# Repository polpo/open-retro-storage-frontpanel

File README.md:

# Open Retro Storage Front Panel

A physical control and web interface for retro storage emulator projects including [PicoIDE](https://github.com/polpo/picoide) and [BlueSCSI](https://github.com/BlueSCSI/BlueSCSI-v2), based on the ESP32-C3 microcontroller.

## Overview

The Open Retro Storage Front Panel provides a user-friendly interface for browsing, selecting, and managing drive images for storage emulators live on the device. It features:

- **SPI or I2C (Qwiic) connection to main board**
- **SPI OLED Display**: 128x64 1.3" screen for menu navigation and status display
- **4-Way Navigation**: Physical buttons for browsing drive images and settings
- **WiFi Interface**: Web-based control for changing drive images, adjusting settings, uploading new images, and firmware updates
- **3.5" Drive Bay Enclosure**: Designed for internal or external-facing mounting in standard drive bays

## Project Structure

```
open-retro-storage-frontpanel/
├── sw-frontpanel/       # Firmware source code
├── hw-frontpanel-3.5/   # PCB hardware design
└── enclosure/           # 3D printable enclosure design
```

### sw-frontpanel

ESP32-C3 firmware built with the ESP-IDF SDK (v5.5.1+).

**Features:**
- SPI or I2C (Qwiic) communication with host storage emulator
- Menu system for drive image browsing and selection
- WiFi client and access point modes with mDNS
- Embedded web server with REST API
- OTA firmware updates with SHA256 verification
- WS2812B addressable LED support
- Screen saver, auto-dim, or auto-off to preserve OLED display life

### hw-frontpanel-3.5

KiCad design files for the front panel PCB.

**Main components:**
- ESP32-C3-MINI-1 module
- SH1107 1.3" OLED display (SPI interface)
- SK6812MINI-E (WS2812 compatible) addressable RGB LED
- Navigation buttons (either 1-piece silicone rubber dome or plastic button caps w/ individual domes)
- JST-SH connectors for QWIIC/I2C communication with host, external activity LED input, and development debugging, 0.5mm FFC connector for SPI communication with host, and Tag-Connect footprint for initial programming in production

Connector pinouts:

SPI (0.5mm FFC, 12 pin):

| Pin | Function |
|-----|----------|
| 1   | Activity LED in |
| 2   | GND |
| 3   | SPI CS |
| 4   | GND |
| 5   | SPI CLK |
| 6   | GND |
| 7   | SPI RX (MISO) |
| 8   | GND |
| 9   | SPI TX (MOSI) |
| 10  | GND |
| 11  | +3.3V |
| 12  | +3.3V |

I2C/Qwiic (JST-SH, 4 pin):

| Pin | Function |
|-----|----------|
| 1   | GND|
| 2   | +3.3V |
| 3   | SDA |
| 4   | SCL |

ACT (JST-SH, 2 pin):

| Pin | Function |
|-----|----------|
| 1   | Activity LED in |
| 2   | GND |

Production files for JLCPCB assembly are included in `jlcpcb/production_files/`.

### enclosure

FreeCAD design for a 3.5" drive bay enclosure with STEP and STL exports for 3D printing.

**Included parts:**
- Main enclosure body
- Button caps
- Light pipe for activity/status LED
- Silicone button option

## Web Interface

The front panel hosts a web interface accessible at `http://picoide.local` (or via IP address) providing:

- Current drive image status
- Directory browsing
- File upload/download
- Config .ini file editing
- Image selection/ejection
- Firmware status and updates

## Licensing

| Component | License |
|-----------|---------|
| sw-frontpanel | [GPL-2.0-only](sw-frontpanel/LICENSE) |
| hw-frontpanel-3.5 | [CERN-OHL-S-2.0](hw-frontpanel-3.5/LICENSE) |
| enclosure | [CERN-OHL-S-2.0](enclosure/LICENSE) |

## Credits

- Firmware by Ian Scott in collaboration with Eric Helgeson.
- Board design by Ian Scott with input from Jason Merrill.
- Enclosure by Jason Merrill.

## Open source components

- [ESP-IDF](https://github.com/espressif/esp-idf) development framework for ESP32
- [u8g2](https://github.com/olikraus/u8g2) graphics library for OLED
- [u8g2-hal-esp-idf](https://github.com/mkfrey/u8g2-hal-esp-idf) u8g2 HAL layer for ESP-IDF

## Contributing

Contributions are welcome! Please ensure any firmware contributions maintain GPL v2 compatibility and hardware contributions are compatible with CERN-OHL-S v2.

## Building the firmware

Make sure you check out this repository with submodules. If it's already checked out, `git submodule update --init` will fetch them. See [sw-frontpanel/BUILD.md](sw-frontpanel/BUILD.md) for detailed instructions including configuration of target type (PicoIDE/BlueSCSI, SPI/I2C).

## Programming the firmware

For normal firmware upgrades, the front panel can be upgraded via the web interface. But if you're building from scratch or need to recover a bricked unit, you'll need to program the ESP32-C3 by UART bootloader.

There are two footprints on the board that can be used to program it: J4 (prog) and J6 (dbg). J4 is a [Tag-Connect](https://www.tag-connect.com/) footprint, using the [TC2030-IDC-NL](https://www.tag-connect.com/product/tc2030-idc-nl) connector. The pinout matches the 6-pin connector on the [Espressif ESP-PROG 2](https://docs.espressif.com/projects/esp-dev-kits/en/latest/other/esp-prog-2/user_guide.html) programmer:

| Pin | Function |
|-----|----------|
| 1   | EN (RTS) |
| 2   | +3.3V |
| 3   | TX |
| 4   | GND |
| 5   | RX |
| 6   | IO0 (DTR) |

J6 is a JST SH 5-pin connector with the following pinout (pins numbered ascending left to right):

| Pin | Function |
|-----|----------|
| 1   | GND |
| 2   | RX |
| 3   | TX |
| 4   | EN (RTS) |
| 5   | IO0 (DTR) |

Note that J6 does not carry +3.3V so you'll have to provide it on the SPI or I2C (QWIIC) connector.

Note that the TX signal is shared with the LED input, so if it is driven via the SPI connector programming will not be possible.

Use `esptool` or `esp.py program` to program the firmware after it has been built.

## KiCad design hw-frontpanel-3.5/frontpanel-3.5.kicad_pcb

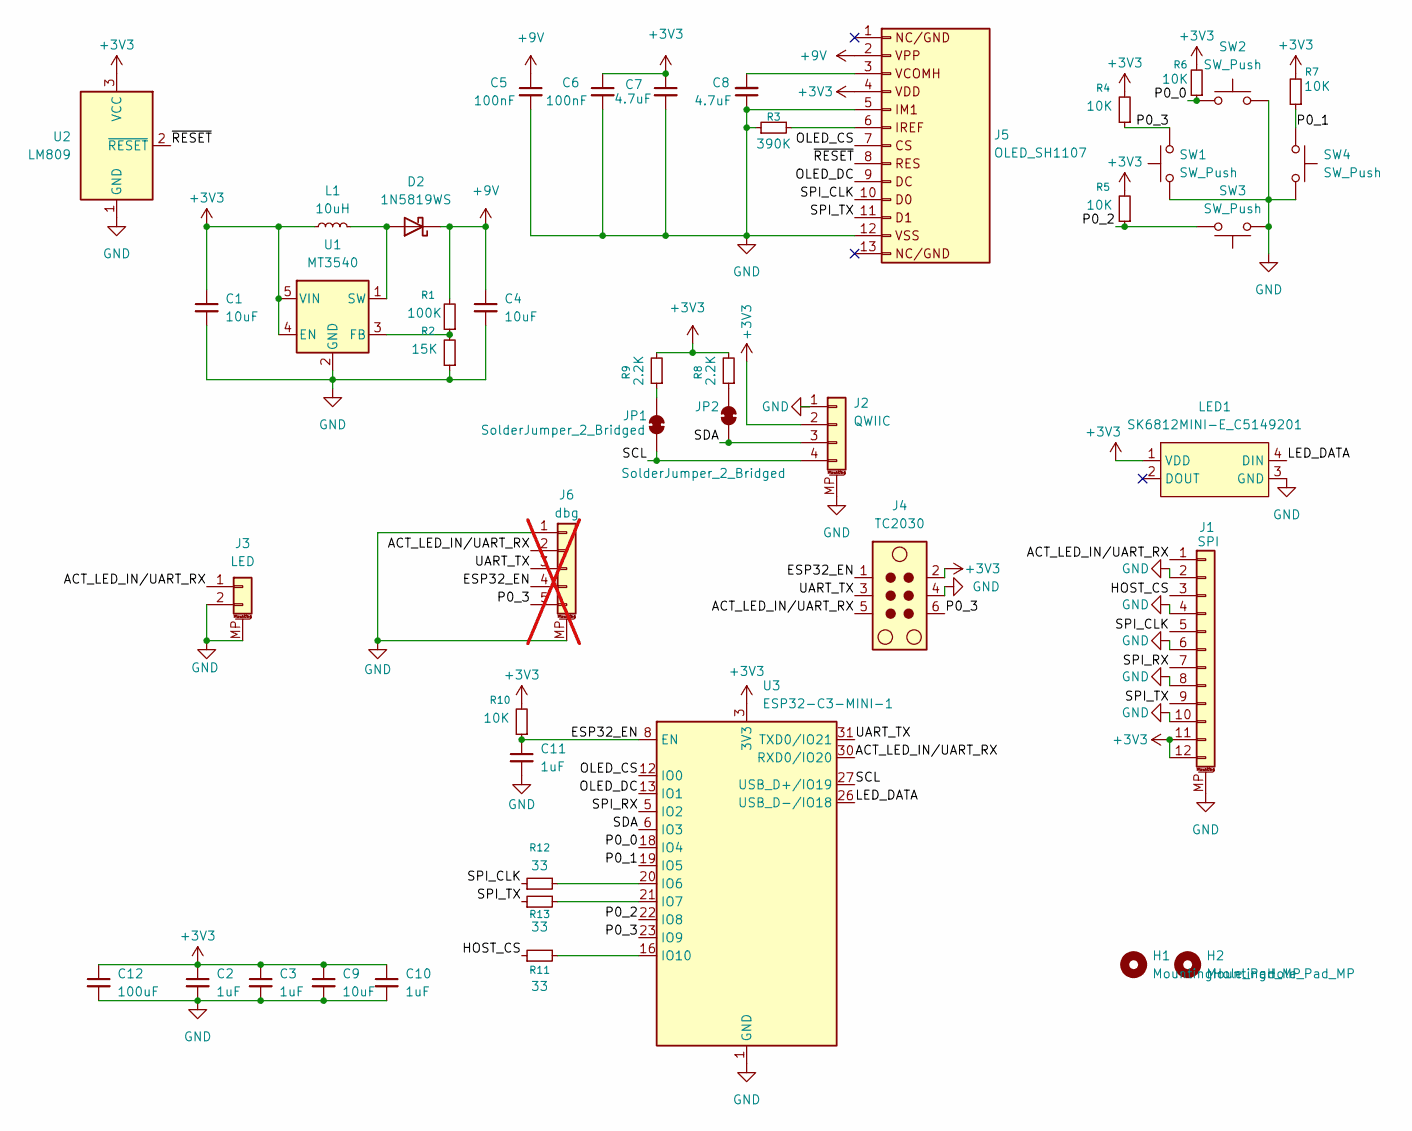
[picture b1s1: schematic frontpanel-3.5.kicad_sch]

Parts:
C1, C4: 10uF; C_0603_1608Metric; LCSC C96446
C2, C3, C10, C11: 1uF; C_0402_1005Metric; LCSC C15849
C5, C6: 100nF; C_0402_1005Metric; LCSC C14663
C7, C8: 4.7uF; C_0603_1608Metric; LCSC C19666
C9: 10uF; C_0603_1608Metric
C12: 100uF; C_1206_3216Metric; LCSC C96123
D2: 1N5819WS; D_SOD-323; LCSC C191023
H1, H2: MountingHole_Pad_MP; MountingHole_2.2mm_M2
J1: SPI; FPC-SMD_12P-L11.5-W2.0-P0.50; LCSC C2874482
J2: QWIIC; JST_SH_BM04B-SRSS-TB_1x04-1MP_P1.00mm_Vertical; LCSC C23390346
J3: LED; JST_SH_BM02B-SRSS-TB_1x02-1MP_P1.00mm_Vertical; LCSC C22438427
J4: TC2030; Tag-Connect_TC2030-IDC-NL_2x03_P1.27mm_Vertical
J5: OLED_SH1107; OLED-SMD_N130-6428TSWOG01-H13
J6: dbg; JST_SH_BM05B-SRSS-TB_1x05-1MP_P1.00mm_Vertical; LCSC C22438427; not fitted
JP1, JP2: SolderJumper_2_Bridged; SolderJumper-2_P1.3mm_Bridged_RoundedPad1.0x1.5mm
L1: 10uH; L_0805_2012Metric; LCSC C1046
LED1: SK6812MINI-E_C5149201; LED-SMD_L3.2-W2.8-LS5.9_SK6812MINI-E; LCSC Part C5149201
R1: 100K; R_0402_1005Metric; LCSC C25803
R2: 15K; R_0402_1005Metric; LCSC C22809
R3: 390K; R_0402_1005Metric; LCSC C23150
R4, R5, R6, R7, R10: 10K; R_0402_1005Metric; LCSC C25804
R8, R9: 2.2K; R_0402_1005Metric; LCSC C4190
R11, R12, R13: 33; R_0402_1005Metric
SW1, SW2, SW3, SW4: SW_Push; button-contact-round-5mm
U1: MT3540; SOT-23-5; LCSC C181744
U2: LM809; SOT-23; LCSC C5379074
U3: ESP32-C3-MINI-1; ESP32-C6-MINI-1; LCSC C2838502

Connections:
+3V3: C1.1, C2.1, C3.1, C6.1, C7.1, C9.1, C10.1, C12.1, J1.11, J1.12, J2.2, J4.2, J5.4, L1.1, LED1.1 (VDD), R4.2, R5.2, R6.2, R7.2, R8.2, R9.2, R10.2, U1.4 (EN), U1.5 (VIN), U2.3 (VCC), U3.3 (3V3)
+9V: C4.1, C5.1, D2.1 (K), J5.2, R1.2
/ACT_LED_IN/UART_RX: J1.1, J3.1, J4.5, J6.2, U3.30 (RXD0/IO20)
/ESP32_EN: C11.1, J4.1, J6.4, R10.1, U3.8 (EN)
/HOST_CS: J1.3, R11.1
/LED_DATA: LED1.4 (DIN), U3.26 (USB_D-/IO18)
/OLED_CS: J5.7, U3.12 (IO0)
/OLED_DC: J5.9, U3.13 (IO1)
/P0_0: R6.1, SW2.1, U3.18 (IO4)
/P0_1: R7.1, SW4.1, U3.19 (IO5)
/P0_2: R5.1, SW3.2, U3.22 (IO8)
/P0_3: J4.6, J6.5, R4.1, SW1.2, U3.23 (IO9)
/SCL: J2.4, JP1.1 (A), U3.27 (USB_D+/IO19)
/SDA: J2.3, JP2.1 (A), U3.6 (IO3)
/SPI_CLK: J1.5, J5.10, R12.1
/SPI_RX: J1.7, U3.5 (IO2)
/SPI_TX: J1.9, J5.11, R13.1
/UART_TX: J4.3, J6.3, U3.31 (TXD0/IO21)
/~RESET: J5.8, U2.2 (~RESET)
GND: C1.2, C2.2, C3.2, C4.2, C5.2, C6.2, C7.2, C8.1, C9.2, C10.2, C11.2, C12.2, J1.2, J1.4, J1.6, J1.8, J1.10, J1.MP (MountPin), J2.1, J2.MP (MountPin), J3.2, J3.MP (MountPin), J4.4, J5.5, J5.12, J6.1, J6.MP (MountPin), LED1.3 (GND), R2.1, R3.1, SW1.1, SW2.2, SW3.1, SW4.2, U1.2 (GND), U2.1 (GND), U3.1 (GND), U3.2 (GND), U3.11 (GND), U3.14 (GND), U3.36 (GND), U3.37 (GND), U3.38 (GND), U3.39 (GND), U3.40 (GND), U3.41 (GND), U3.42 (GND), U3.43 (GND), U3.44 (GND), U3.45 (GND), U3.46 (GND), U3.47 (GND), U3.48 (GND), U3.49 (GND), U3.50 (GND), U3.51 (GND), U3.52 (GND), U3.53 (GND)
unnamed: D2.2 (A), L1.2, U1.1 (SW)
unnamed: C8.2, J5.3
unnamed: J5.6, R3.2
unnamed: JP1.2 (B), R9.1
unnamed: JP2.2 (B), R8.1
unnamed: R1.1, R2.2, U1.3 (FB)
unnamed: R12.2, U3.20 (IO6)
unnamed: R13.2, U3.21 (IO7)
unnamed: R11.2, U3.16 (IO10)

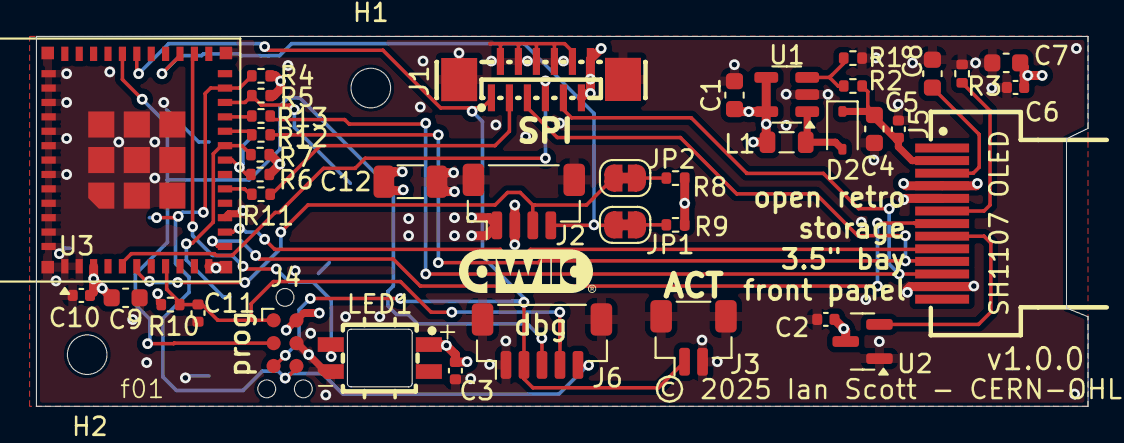
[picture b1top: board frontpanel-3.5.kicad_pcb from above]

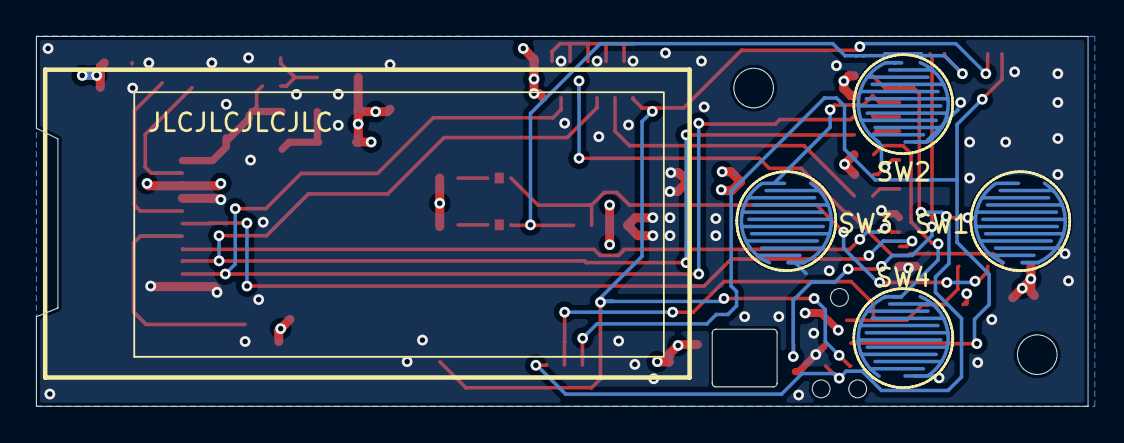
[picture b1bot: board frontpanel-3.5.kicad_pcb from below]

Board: 4 copper layers, 58.4 x 20.5 mm, 45 parts (4 on the bottom side), 29 nets.

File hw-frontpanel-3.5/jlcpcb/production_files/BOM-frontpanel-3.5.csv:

Comment,Designator,Footprint,LCSC,Quantity
100K,R1,R_0402_1005Metric,C25741,1
100nF,"C5,C6",C_0402_1005Metric,C307331,2
100uF,C12,C_1206_3216Metric,C96123,1
10K,"R10,R4,R5,R6,R7",R_0402_1005Metric,C25744,5
10uF,"C1,C4,C9",C_0603_1608Metric,C96446,3
10uH,L1,L_0805_2012Metric,C1046,1
15K,R2,R_0402_1005Metric,C25756,1
1N5819WS,D2,D_SOD-323,C191023,1
1uF,"C10,C11,C2,C3",C_0402_1005Metric,C52923,4
2.2K,"R8,R9",R_0402_1005Metric,C25879,2
33,"R11,R12,R13",R_0402_1005Metric,C25105,3
390K,R3,R_0402_1005Metric,C25782,1
4.7uF,"C7,C8",C_0603_1608Metric,C19666,2
ESP32-C3-MINI-1,U3,ESP32-C6-MINI-1,C2838502,1
LED,J3,JST_SH_BM02B-SRSS-TB_1x02-1MP_P1.00mm_Vertical,C7433438,1
LM809,U2,SOT-23,C5379074,1
MT3540,U1,SOT-23-5,C181744,1
QWIIC,J2,JST_SH_BM04B-SRSS-TB_1x04-1MP_P1.00mm_Vertical,C7433440,1
SK6812MINI-E_C5149201,LED1,LED-SMD_L3.2-W2.8-LS5.9_SK6812MINI-E,C5149201,1
SPI,J1,FPC-SMD_12P-L11.5-W2.0-P0.50,C11069,1

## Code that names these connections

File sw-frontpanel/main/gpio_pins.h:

// SPDX-License-Identifier: GPL-2.0-only
//
//  Copyright (C) 2025  Ian Scott
//
//  This program is free software; you can redistribute it and/or modify it
//  under the terms of the GNU General Public License (as published by the
//  Free Software Foundation) version 2, dated June 1991.
//
//  This program is distributed in the hope that it will be useful,
//  but WITHOUT ANY WARRANTY; without even the implied warranty of
//  MERCHANTABILITY or FITNESS FOR A PARTICULAR PURPOSE.  See the
//  GNU General Public License for more details.
//
//  You should have received a copy of the GNU General Public License along
//  with this program; if not, see <https://www.gnu.org/licenses/>.

#pragma once

#include "driver/gpio.h"
#include "sdkconfig.h"

#ifdef CONFIG_PANEL_BOARD_C3_SUPERMINI

// ESP32-C3 SuperMini (DIY, web UI only).
//
// That board brings out GPIO0-10, GPIO20 and GPIO21 and nothing else: GPIO18
// and GPIO19 are wired to its USB-C data lines, and GPIO11-17 are the module's
// SPI flash. Three of the remaining pins are spoken for by the board itself -
// GPIO8 drives the onboard blue LED, GPIO9 is the BOOT button, GPIO2 carries
// the strapping pull-up - and GPIO20/21 are the UART console. That leaves
// eight: GPIO0, 1, 3, 4, 5, 6, 7 and 10.
//
// Both host transports get their own pins, so one image runs on every main
// board. That spends all eight, which is why this board has no OLED
// (CONFIG_PANEL_NO_DISPLAY) and no navigation buttons
// (CONFIG_PANEL_NO_BUTTONS) - the web UI drives it instead.
//
// The SPI pins deliberately avoid the SPI2 IO_MUX set (MISO 2, CLK 6, MOSI 7,
// CS 10). IO_MUX would allow 80 MHz against the GPIO matrix's 40, and the host
// link runs at 10 - so there is nothing to win, and IO_MUX MISO would land on
// GPIO2, whose strapping level a host driving the line at reset could hold low.

// Host interface, I2C (BlueSCSI v2): GPIO3 -> host GPIO16,
// GPIO10 -> host GPIO17, plus 2.2k pull-ups to 3V3 on both.
#define PIN_SDA         GPIO_NUM_3
#define PIN_SCL         GPIO_NUM_10

// Host interface, SPI (BlueSCSI Ultra/Ultra Wide, PicoIDE).
//
// PicoIDE's 12-pin panel ribbon. RX and TX are named from the PicoIDE side,
// so they cross. A ground sits between every signal; tie them all on a long
// ribbon to keep the 10 MHz clock quiet.
//
//   1, 2            3V3       3V3 (the panel runs off this)
//   3, 5, 7, 9, 11  GND       GND
//   4               SPI_RX    GPIO7  (MOSI)
//   6               SPI_TX    GPIO5  (MISO)
//   8               SPI_CLK   GPIO6
//   10              SPI_CS    GPIO4
//   12              ACT_LED   GPIO0
#define PIN_SPI_CLK     GPIO_NUM_6
#define PIN_SPI_MOSI    GPIO_NUM_7
#define PIN_SPI_MISO    GPIO_NUM_5
#define PIN_HOST_CS     GPIO_NUM_4

// Activity indicator input (from main board). Unconnected on most DIY builds,
// so gpio_handler pulls it up - a floating pin would storm the edge ISR.
#define PIN_ACT_IN      GPIO_NUM_0

// LED output (WS2812B addressable LED strip), optional.
#define PIN_LED_OUT     GPIO_NUM_1

// UART interface (USB-C console)
#define PIN_UART_TX     GPIO_NUM_21

// No OLED on this board. These stay defined so the display paths still
// compile; CONFIG_PANEL_NO_DISPLAY means they are never driven.
#define PIN_OLED_CS     GPIO_NUM_NC
#define PIN_OLED_DC     GPIO_NUM_NC

#else

// OLED Display control pins (SPI mode)
#define PIN_OLED_CS     GPIO_NUM_0   // Chip Select for SPI OLED
#define PIN_OLED_DC     GPIO_NUM_1   // Data/Command for SPI OLED

// SPI interface pins (shared by OLED display and future SPI devices)
#define PIN_SPI_MISO    GPIO_NUM_2   // Master In Slave Out (not used by OLED)
#define PIN_SPI_CLK     GPIO_NUM_6   // SPI Clock
#define PIN_SPI_MOSI    GPIO_NUM_7   // Master Out Slave In (OLED data)

// Activity indicator input (from main board)
#define PIN_ACT_IN      GPIO_NUM_20

// Navigation button pins
#define PIN_NAV_UP      GPIO_NUM_4
#define PIN_NAV_RIGHT   GPIO_NUM_9
#define PIN_NAV_DOWN    GPIO_NUM_5
#define PIN_NAV_LEFT    GPIO_NUM_8

// Host interface chip select
#define PIN_HOST_CS     GPIO_NUM_10

// LED output (WS2812B addressable LED strip)
#define PIN_LED_OUT     GPIO_NUM_18

// I2C interface pins (for communication with main board)
#define PIN_SCL         GPIO_NUM_19  // I2C Clock
#define PIN_SDA         GPIO_NUM_3  // I2C Data

// UART interface
#define PIN_UART_TX     GPIO_NUM_21

#endif // CONFIG_PANEL_BOARD_C3_SUPERMINI

// LED strip configuration
#define LED_STRIP_GPIO_NUM  PIN_LED_OUT

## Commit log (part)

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2025-08-26 Front panel proto fabbed at JLC 2025-08-26
2025-09-07 Support EVT1 board
2025-09-07 Front panel ESP32 firmware
2025-09-17 Allow u8g2 to use already-configured SPI so we can use MISO
2025-09-17 Cleanup
2025-09-17 Move frontpanel to esp32-c3
2025-09-17 Super basic RGB LED support
2025-09-17 Working SPI communication between main board and front panel. I2C was working but now untested
2025-09-17 frontpanel: WiFi, mdns, and web server
2025-09-18 Front panel board fabbed at JLCPCB 2025-09-17
2025-09-19 Mostly working protocol between RP2350 and ESP32
2025-09-22 More reliable SPI comms between main and front panel boards
2025-09-22 Update ESP32 sdkconfig for 4MB flash
2025-09-22 Check SHA hash after upload because calculating upfront blocks
2025-09-23 Working frontpanel firmware update from SD card via main board
2025-09-24 Lock dependencies and change u8g2 to submodule
2025-09-27 Better working splash screen, firmware update, faster SPI
2025-09-27 Basic disc status reporting
2025-09-30 Smoothly scroll long disc names, refactor/cleanup display & menus
2025-10-02 Make LED less blinding
2025-10-02 Fix scrolling of menu items
2025-10-07 Added the enclosure Step files and FreeCAD files.
2025-10-12 Checkpoint for dynamic ide/atapi modes
2025-10-26 Add config for panelization of main board
2025-11-04 many changes made to the enclosure
2025-11-14 added bluescsi holes made mounting holes smaller added internal mounting holes made the picoide logo it's own object
2025-11-14 fixed corrupt file error
2025-11-18 added silicone buttons
2025-11-18 added exhaust channels to silicone buttons
2025-11-21 tweaked for molding feedback and added second logo plate
2025-11-27 Commit front panel firmware update if successful
2025-11-27 Delay between SPI transport phases when in debug
2025-11-28 Checkpoint for firmware update via front panel
2025-11-29 Firmware update fixes
2025-11-29 Use RC for ESP32 reset, power on reset for OLED
2025-11-29 Provisional v1.0.0 hardware
2025-11-30 Refactor menus on front panel and improve wifi mgmt
2025-12-23 Final candidate v1.0.0 hardware
2025-12-23 Front panel UI updates
2025-12-31 Add licensing
2025-12-31 Fix u8g2 submodule
2025-12-31 Add action to build firmware
2025-12-31 Final v1.0.0 front panel design
2025-12-31 Add README
2026-01-04 modular faceplate made better and added steps and stls
2026-01-08 Firmware v0.2.1
2026-01-08 Better display of main/front panel FW versions
2026-01-08 Fix for keypress to wake up display passing through as event
2026-01-08 Firmware v0.2.0
2026-01-08 Better handling of image status, handle fixed HDDs on status screen
2026-01-08 Fix menu scrolling
2026-01-08 Fix display glitch on firmware update screen
2026-01-08 Firmware v0.2.2
2026-01-08 Add changelog
2026-01-11 Add build instructions to README
2026-01-11 Minify/gzip static web assets during fw build
2026-01-11 Fix fetching front panel fw update status timeouts
2026-01-11 Wrap host comm transactions in semaphore to prevent async ops from stomping on each other
2026-01-11 Make front panel firmware check more in line with main board firmware check
2026-01-11 picoide.ini editor component, arbitrary file upload/download commands
2026-01-11 Wifi status improvements
2026-01-11 Run requests in series on page load
2026-01-11 Nicer status bar
2026-01-11 Dark mode, layout improvements, add PicoIDE logo
2026-01-11 Firmware v0.3.0
2026-01-30 added the bluescsi screw adapter and moved the front screw boss back based on molding feedback
2026-01-30 added stl for bluescsi screw adapter
2026-02-03 final changes (hopefully) for molding
2026-02-06 Fix crash when no images on SD card.
2026-02-08 more tweaks
2026-02-17 nix build env
2026-02-17 Initial BlueSCSI Support - many things WIP.
2026-02-18 Initial multi-device
2026-02-19 eject indicator
2026-02-19 fixup bluescsi fw version string as date
2026-02-19 ifdef some quirks for bluescsi timeouts - may not be required in the end.
2026-02-19 test gh action
2026-02-19 dynamic polling interval as we're not always playing a cd
2026-02-19 Collapse WiFi config section when already connected Check BlueSCSI GitHub releases for main board update availability Show free memory in KB, uptime as min:sec Disable spellcheck on config editor Cou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
2026-02-19 Make both tables look the same
2026-02-19 Dont show error if optional file does not exist
2026-02-27 made holes bigger for buttons so silicone buttons don't stick anymore.
2026-05-16 Add screen savers
2026-05-16 Combine firmware update & allow prereleases
2026-05-16 Update changelog
2026-05-20 Better reporting of disc status, configurable timeout for display blanking
2026-05-20 Correctly report main/panel firmware versions in web interface
2026-05-20 Hook up main board liveness checking
2026-05-20 Renumber statuses so main board can detect if we're dead/disconnected
2026-05-20 Change labels for idle/blank timeouts
2026-05-20 Only show main board firmware during bootup
2026-05-20 Undo renumbering of enums for liveness check, use magic value instead
2026-05-20 v0.4.0-pre2
2026-06-01 Use "liveness magic" on PicoIDE to better determine if main board is alive
2026-06-01 Be more resilient if main board is not ready at startup
2026-06-01 Build fixes
2026-06-01 v0.4.0-pre3
2026-06-01 Add missing fw_version
2026-06-05 Sync ejectable device types with BlueSCSI
2026-06-05 Fix web-asset build on Nix and update flake inputs
2026-06-05 Add BUILD.md with per-product build instructions
    Document how to build the PicoIDE and BlueSCSI variants via the
    SDKCONFIG_DEFAULTS overlays into separate per-product build dirs,
    plus dev environment, flashing, and cleaning steps.
2026-06-05 Unify BlueSCSI/PicoIDE front-panel behavior; remove product ifdefs
2026-06-05 Isolate per-product sdkconfig in build instructions and CI
2026-06-05 Ignore per-product build-*/ directories
2026-06-05 Update GitHub Actions runtimes off deprecated Node versions
2026-06-05 Refresh file browser after upload if still in that directory
2026-06-05 Add direct firmware upload to ESP32 front panel
    For BlueSCSI, make the direct upload the primary panel-update path.
2026-06-05 Default panel to first removable device instead of device 0
2026-06-05 Hide Prev/Next image buttons on BlueSCSI web UI
    Currently we just eject to cycle or select from UI. May add prev later.
2026-06-07 indicate optical tray-open state on LCD and web
2026-06-07 Add download, delete, rename, new file and new folder to web image browser
2026-06-07 Relicense panel_protocol_defs.h to GPL-2.0-or-later
    Allows this shared protocol header to be included in GPLv3+ projects
    (e.g. BlueSCSI). Only this file is relicensed; the rest of the project
    remains GPL-2.0-only. Done with the consent of all copyright holders.
2026-06-08 Implement I2C transport async polling
    Implement transport_i2c_poll_async_status() (mirroring the SPI path) and
    move the POLL_OP_READY ready/result read out of two_phase_transaction.
    Guard transport_poll_async_status against a NULL op so a transport that
    does not implement it returns ESP_ERR_NOT_SUPPORTED instead of crashing.
    Add an I2C inter-phase delay knob.
2026-06-08 Add bluescsi-v2 (I2C) front-panel build variant
    Make the host transport a Kconfig choice (HOST_TRANSPORT_SPI/_I2C),
    orthogonal to product and selected per-build via sdkconfig.defaults.i2c.
    BlueSCSI Ultra and PicoIDE keep SPI; BlueSCSI v2 uses I2C and builds as
    bluescsi-v2-frontpanel.bin. Update BUILD.md and the CI matrix.
2026-06-09 Bump panel I2C to 1 MHz and shrink the inter-phase delay
    Raise the I2C host clock from 400 kHz to 1 MHz (fast-mode-plus) and drop the
    header-to-read inter-phase delay from 1 ms to 200 us, using esp_rom_delay_us()
    for real microsecond granularity (vTaskDelay only resolves milliseconds). The
    slave prepares its read response in the ISR, so the long delay was unnecessary.
2026-06-09 Add host-native unit tests for the protocol and host-comm layer
    Compile host_comm.c and transport.c against ESP-IDF/FreeRTOS stubs and a
    recording mock transport, covering the panel_protocol_defs.h wire contract
    (struct packing, command bits) and host_comm command framing. Runs as the
    host-tests CI job; needs only host gcc + make.
2026-06-09 Quiet per-transaction I2C transport logging
    Drop the phase-by-phase ESP_LOGD traces and payload hex dump from the
    I2C transport hot path, and move file-op result codes to debug level.
    Errors and operation-start logs are unchanged.
2026-06-09 Retry NACKed I2C transactions and fold file ops onto one path-op helper
    A busy I2C slave NACKs its address (no clock stretching on the RP2040
    side), which previously surfaced as an immediate error; retry the
    transaction up to I2C_RETRY_COUNT times so transient busy windows behave
    like SPI, where the master always clocks and readiness is handled by
    POLL_OP_READY. Also collapse delete/rename/touch/mkdir onto a single
    host_comm_path_op helper (same wire format) and drop the unused
2026-06-09 Name the BlueSCSI SPI firmware bluescsi-ultra and release all variant bins
    bluescsi-frontpanel.bin was ambiguous next to bluescsi-v2-frontpanel.bin;
    name each image after the host board it pairs with (Ultra/Ultra Wide vs
    v2) so users can pick the right file. Also attach the two BlueSCSI bins
    to GitHub releases, which previously shipped only the PicoIDE image.
2026-06-10 updated the bluescsi 3.5 enclosure
2026-06-11 added supports for bosses
2026-06-11 Address PR review: pass bools directly and use HTTPD_RESP_USE_STRLEN

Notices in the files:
hw-frontpanel-3.5/frontpanel-3.5.kicad_pcb:
© 2025 Ian Scott - CERN-OHL-S v2
